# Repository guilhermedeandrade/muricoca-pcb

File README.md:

# Muriçoca PCB

## Supported layout

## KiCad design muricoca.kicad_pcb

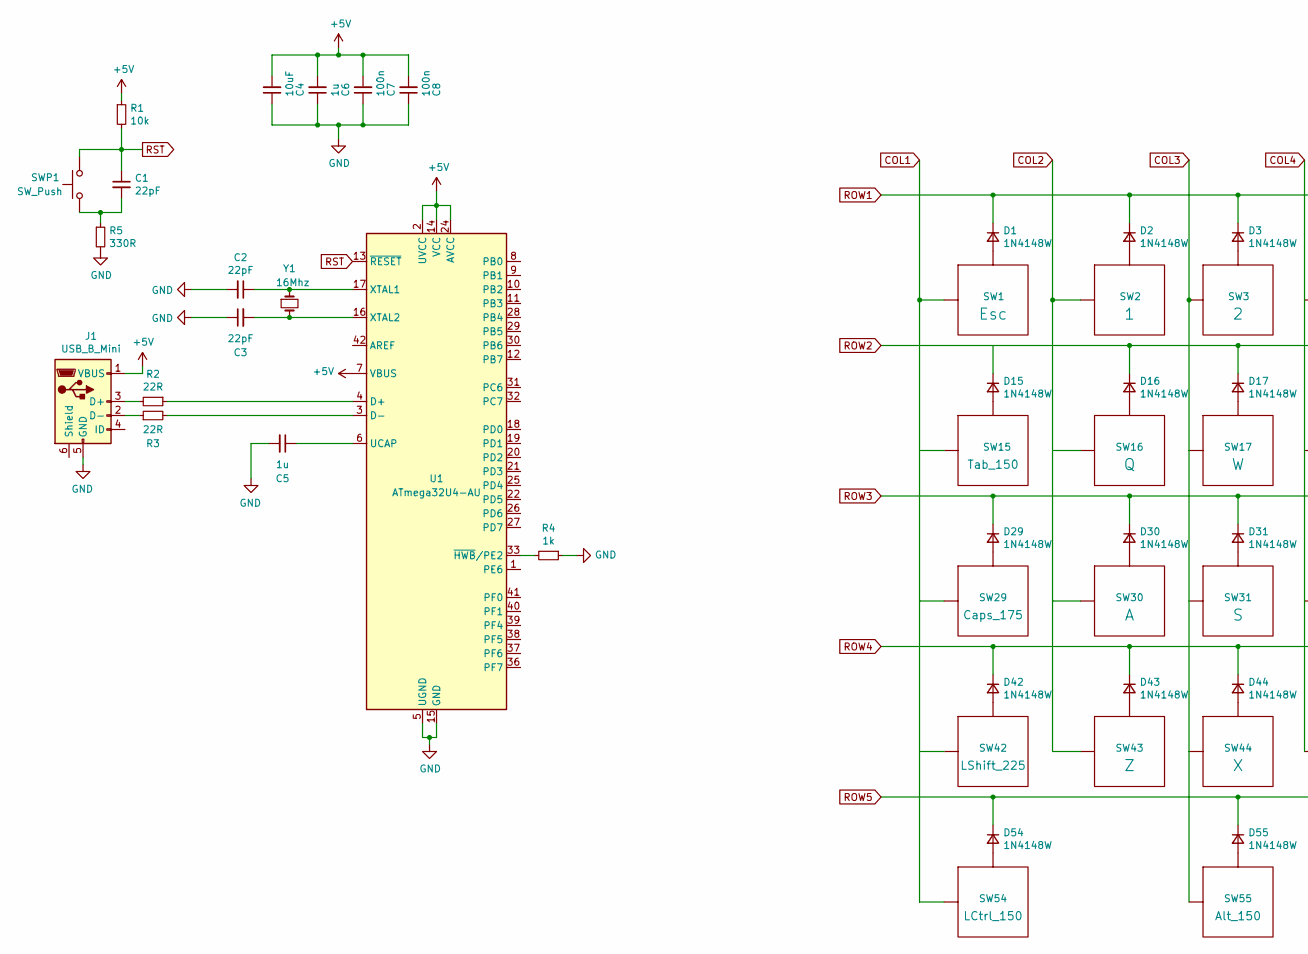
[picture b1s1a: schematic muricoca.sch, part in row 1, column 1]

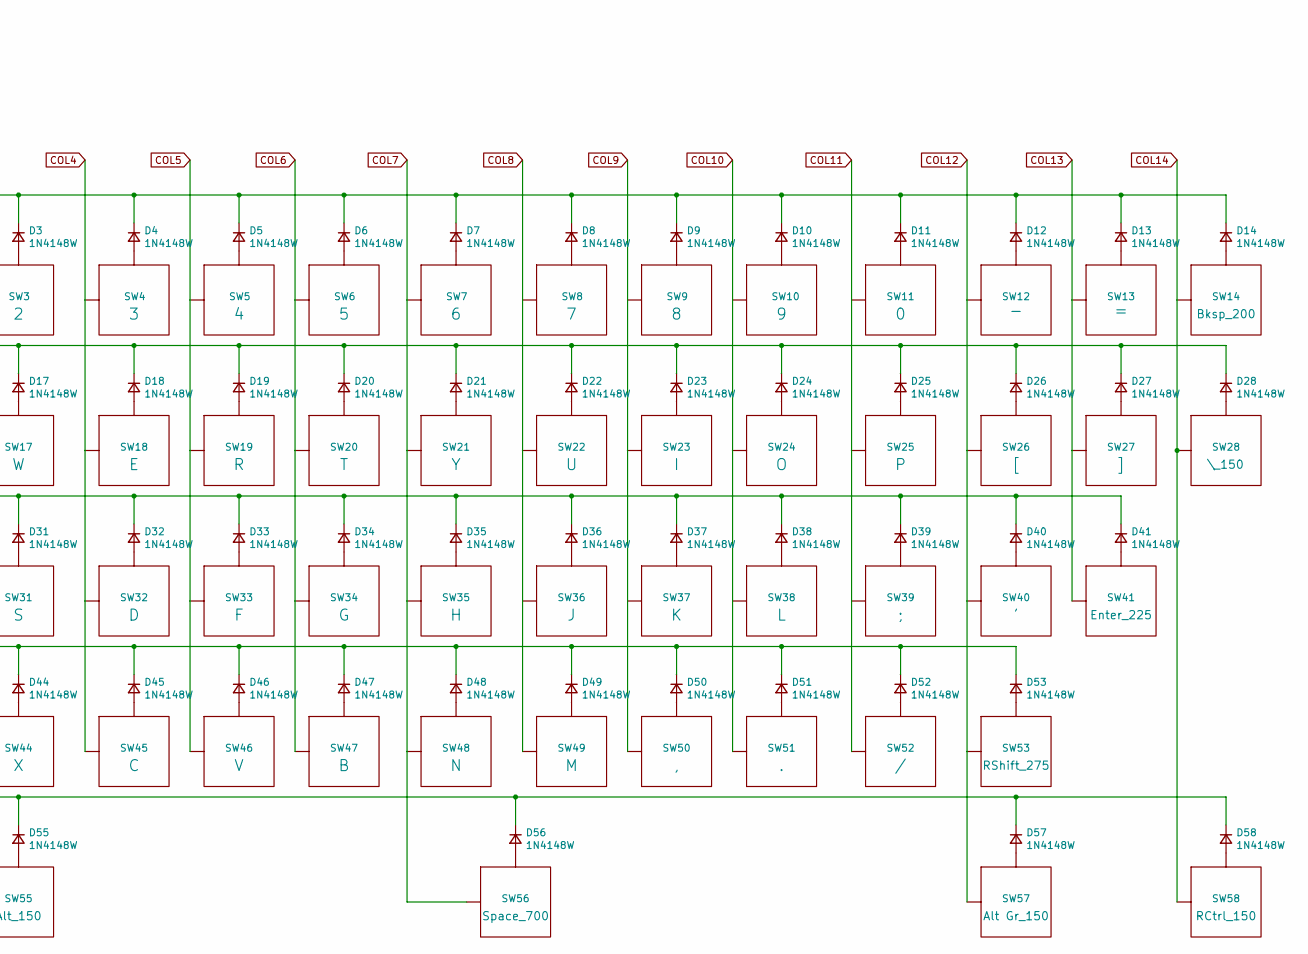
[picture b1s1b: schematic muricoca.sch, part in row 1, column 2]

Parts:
C1, C2, C3: 22pF; C_0805_2012Metric_Pad1.15x1.40mm_HandSolder
C4: 10uF; C_0805_2012Metric_Pad1.15x1.40mm_HandSolder
C5, C6: 1u; C_0805_2012Metric_Pad1.15x1.40mm_HandSolder
C7, C8: 100n; C_0805_2012Metric_Pad1.15x1.40mm_HandSolder
D1, D2, D3, D4, D5, D6, D7, D8, D9, D10, D11, D12, D13, D14, D15, D16, D17, D18, D19, D20, D21, D22, D23, D24, D25, D26, D27, D28, D29, D30, D31, D32, D33, D34, D35, D36, D37, D38, D39, D40, D41, D42, D43, D44, D45, D46, D47, D48, D49, D50, D51, D52, D53, D54, D55, D56, D57, D58: 1N4148W; D_SOD-123
J1: USB_B_Mini; USB_MiniB_XM7D-0512
R1: 10k; R_1206_3216Metric_Pad1.42x1.75mm_HandSolder
R2, R3: 22R; R_1206_3216Metric_Pad1.42x1.75mm_HandSolder
R4: 1k; R_1206_3216Metric_Pad1.42x1.75mm_HandSolder
R5: 330R; R_1206_3216Metric_Pad1.42x1.75mm_HandSolder
SW1: Esc; MX100
SW2: 1; MX100
SW3: 2; MX100
SW4: 3; MX100
SW5: 4; MX100
SW6: 5; MX100
SW7: 6; MX100
SW8: 7; MX100
SW9: 8; MX100
SW10: 9; MX100
SW11: 0; MX100
SW12: -; MX100
SW13: =; MX100
SW14: Bksp_200; MX200
SW15: Tab_150; MX150
SW16: Q; MX100
SW17: W; MX100
SW18: E; MX100
SW19: R; MX100
SW20: T; MX100
SW21: Y; MX100
SW22: U; MX100
SW23: I; MX100
SW24: O; MX100
SW25: P; MX100
SW26: [; MX100
SW27: ]; MX100
SW28: \\_150; MX150
SW29: Caps_175; MX175
SW30: A; MX100
SW31: S; MX100
SW32: D; MX100
SW33: F; MX100
SW34: G; MX100
SW35: H; MX100
SW36: J; MX100
SW37: K; MX100
SW38: L; MX100
SW39: ;; MX100
SW40: '; MX100
SW41: Enter_225; MX225
SW42: LShift_225; MX225
SW43: Z; MX100
SW44: X; MX100
SW45: C; MX100
SW46: V; MX100
SW47: B; MX100
SW48: N; MX100
SW49: M; MX100
SW50: ,; MX100
SW51: .; MX100
SW52: /; MX100
SW53: RShift_275; MX275
SW54: LCtrl_150; MX150
SW55: Alt_150; MX150
SW56: Space_700; MX700
SW57: Alt Gr_150; MX150
SW58: RCtrl_150; MX150
SWP1: SW_Push; SW_Push_1P1T_NO_6x6mm_H9.5mm
U1: ATmega32U4-AU; TQPF-44_10x10mm_P0.8mm
Y1: 16Mhz; Crystal_SMD_5032-2Pin_5.0x3.2mm_HandSoldering

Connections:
+5V: C4.2, C6.2, C7.2, C8.2, J1.1 (VBUS), R1.1, U1.2 (UVCC), U1.7 (VBUS), U1.14 (VCC), U1.24 (AVCC), U1.34 (VCC), U1.44 (AVCC)
COL1: SW1.1 (Col), SW29.1 (Col), SW42.1 (Col), SW54.1 (Col)
COL2: SW2.1 (Col), SW16.1 (Col), SW30.1 (Col), SW43.1 (Col)
COL3: SW3.1 (Col), SW17.1 (Col), SW31.1 (Col), SW44.1 (Col), SW55.1 (Col)
COL4: SW4.1 (Col), SW18.1 (Col), SW32.1 (Col), SW45.1 (Col)
COL5: SW5.1 (Col), SW19.1 (Col), SW33.1 (Col), SW46.1 (Col)
COL6: SW6.1 (Col), SW20.1 (Col), SW34.1 (Col), SW47.1 (Col)
COL7: SW7.1 (Col), SW21.1 (Col), SW35.1 (Col), SW48.1 (Col), SW56.1 (Col)
COL8: SW8.1 (Col), SW22.1 (Col), SW36.1 (Col), SW49.1 (Col)
COL9: SW9.1 (Col), SW23.1 (Col), SW37.1 (Col), SW50.1 (Col)
COL10: SW10.1 (Col), SW24.1 (Col), SW38.1 (Col), SW51.1 (Col)
COL11: SW11.1 (Col), SW25.1 (Col), SW39.1 (Col), SW52.1 (Col)
COL12: SW12.1 (Col), SW26.1 (Col), SW40.1 (Col), SW53.1 (Col), SW57.1 (Col)
COL13: SW13.1 (Col), SW27.1 (Col), SW41.1 (Col)
COL14: SW14.1 (Col), SW28.1 (Col), SW58.1 (Col)
GND: C2.2, C3.1, C4.1, C5.2, C6.1, C7.1, C8.1, J1.5 (GND), R4.1, R5.2, U1.5 (UGND), U1.15 (GND), U1.23 (GND), U1.35 (GND), U1.43 (GND)
unnamed: C1.2, R5.1, SWP1.1
unnamed: C2.1, U1.17 (XTAL1), Y1.1
unnamed: C3.2, U1.16 (XTAL2), Y1.2
unnamed: C5.1, U1.6 (UCAP)
unnamed: D1.2 (A), SW1.2 (Row)
unnamed: D2.2 (A), SW2.2 (Row)
unnamed: D3.2 (A), SW3.2 (Row)
unnamed: D4.2 (A), SW4.2 (Row)
unnamed: D5.2 (A), SW5.2 (Row)
unnamed: D6.2 (A), SW6.2 (Row)
unnamed: D7.2 (A), SW7.2 (Row)
unnamed: D8.2 (A), SW8.2 (Row)
unnamed: D9.2 (A), SW9.2 (Row)
unnamed: D10.2 (A), SW10.2 (Row)
unnamed: D11.2 (A), SW11.2 (Row)
unnamed: D12.2 (A), SW12.2 (Row)
unnamed: D13.2 (A), SW13.2 (Row)
unnamed: D14.2 (A), SW14.2 (Row)
unnamed: D15.2 (A), SW15.2 (Row)
unnamed: D16.2 (A), SW16.2 (Row)
unnamed: D17.2 (A), SW17.2 (Row)
unnamed: D18.2 (A), SW18.2 (Row)
unnamed: D19.2 (A), SW19.2 (Row)
unnamed: D20.2 (A), SW20.2 (Row)
unnamed: D21.2 (A), SW21.2 (Row)
unnamed: D22.2 (A), SW22.2 (Row)
unnamed: D23.2 (A), SW23.2 (Row)
unnamed: D24.2 (A), SW24.2 (Row)
unnamed: D25.2 (A), SW25.2 (Row)
unnamed: D26.2 (A), SW26.2 (Row)
unnamed: D27.2 (A), SW27.2 (Row)
unnamed: D28.2 (A), SW28.2 (Row)
unnamed: D29.2 (A), SW29.2 (Row)
unnamed: D30.2 (A), SW30.2 (Row)
unnamed: D31.2 (A), SW31.2 (Row)
unnamed: D32.2 (A), SW32.2 (Row)
unnamed: D33.2 (A), SW33.2 (Row)
unnamed: D34.2 (A), SW34.2 (Row)
unnamed: D35.2 (A), SW35.2 (Row)
unnamed: D36.2 (A), SW36.2 (Row)
unnamed: D37.2 (A), SW37.2 (Row)
unnamed: D38.2 (A), SW38.2 (Row)
unnamed: D39.2 (A), SW39.2 (Row)
unnamed: D40.2 (A), SW40.2 (Row)
unnamed: D41.2 (A), SW41.2 (Row)
unnamed: D42.2 (A), SW42.2 (Row)
unnamed: D43.2 (A), SW43.2 (Row)
unnamed: D44.2 (A), SW44.2 (Row)
unnamed: D45.2 (A), SW45.2 (Row)
unnamed: D46.2 (A), SW46.2 (Row)
unnamed: D47.2 (A), SW47.2 (Row)
unnamed: D48.2 (A), SW48.2 (Row)
unnamed: D49.2 (A), SW49.2 (Row)
unnamed: D50.2 (A), SW50.2 (Row)
unnamed: D51.2 (A), SW51.2 (Row)
unnamed: D52.2 (A), SW52.2 (Row)
unnamed: D53.2 (A), SW53.2 (Row)
unnamed: D54.2 (A), SW54.2 (Row)
unnamed: D55.2 (A), SW55.2 (Row)
unnamed: D56.2 (A), SW56.2 (Row)
unnamed: D57.2 (A), SW57.2 (Row)
unnamed: D58.2 (A), SW58.2 (Row)
unnamed: J1.2 (D-), R3.1
unnamed: J1.3 (D+), R2.2
unnamed: R2.1, U1.4 (D+)
unnamed: R3.2, U1.3 (D-)
unnamed: R4.2, U1.33 (~HWB~/PE2)
ROW1: D1.1 (K), D2.1 (K), D3.1 (K), D4.1 (K), D5.1 (K), D6.1 (K), D7.1 (K), D8.1 (K), D9.1 (K), D10.1 (K), D11.1 (K), D12.1 (K), D13.1 (K), D14.1 (K)
ROW2: D16.1 (K), D17.1 (K), D18.1 (K), D19.1 (K), D20.1 (K), D21.1 (K), D22.1 (K), D23.1 (K), D24.1 (K), D25.1 (K), D26.1 (K), D27.1 (K), D28.1 (K)
ROW3: D29.1 (K), D30.1 (K), D31.1 (K), D32.1 (K), D33.1 (K), D34.1 (K), D35.1 (K), D36.1 (K), D37.1 (K), D38.1 (K), D39.1 (K), D40.1 (K), D41.1 (K)
ROW4: D42.1 (K), D43.1 (K), D44.1 (K), D45.1 (K), D46.1 (K), D47.1 (K), D48.1 (K), D49.1 (K), D50.1 (K), D51.1 (K), D52.1 (K), D53.1 (K)
ROW5: D54.1 (K), D55.1 (K), D56.1 (K), D57.1 (K), D58.1 (K)
RST: C1.1, R1.2, SWP1.2, U1.13 (~RESET)

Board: 2 copper layers, 133 parts (58 on the bottom side), 89 nets, no tracks yet.

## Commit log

2020-06-06 feat: add matrix first row
2020-06-06 chore: add README
2020-06-06 feat: add matrix second row
2020-06-06 feat: add matrix third row
2020-06-06 feat: add matrix fourth row
2020-06-06 feat: add matrix fifth row
2020-06-06 chore: add keycaps' dimensions to the labels
2020-06-07 chore: assign the correct footprints for the keys bigger than 1u
2020-06-07 feat: align the switches on the PCB
